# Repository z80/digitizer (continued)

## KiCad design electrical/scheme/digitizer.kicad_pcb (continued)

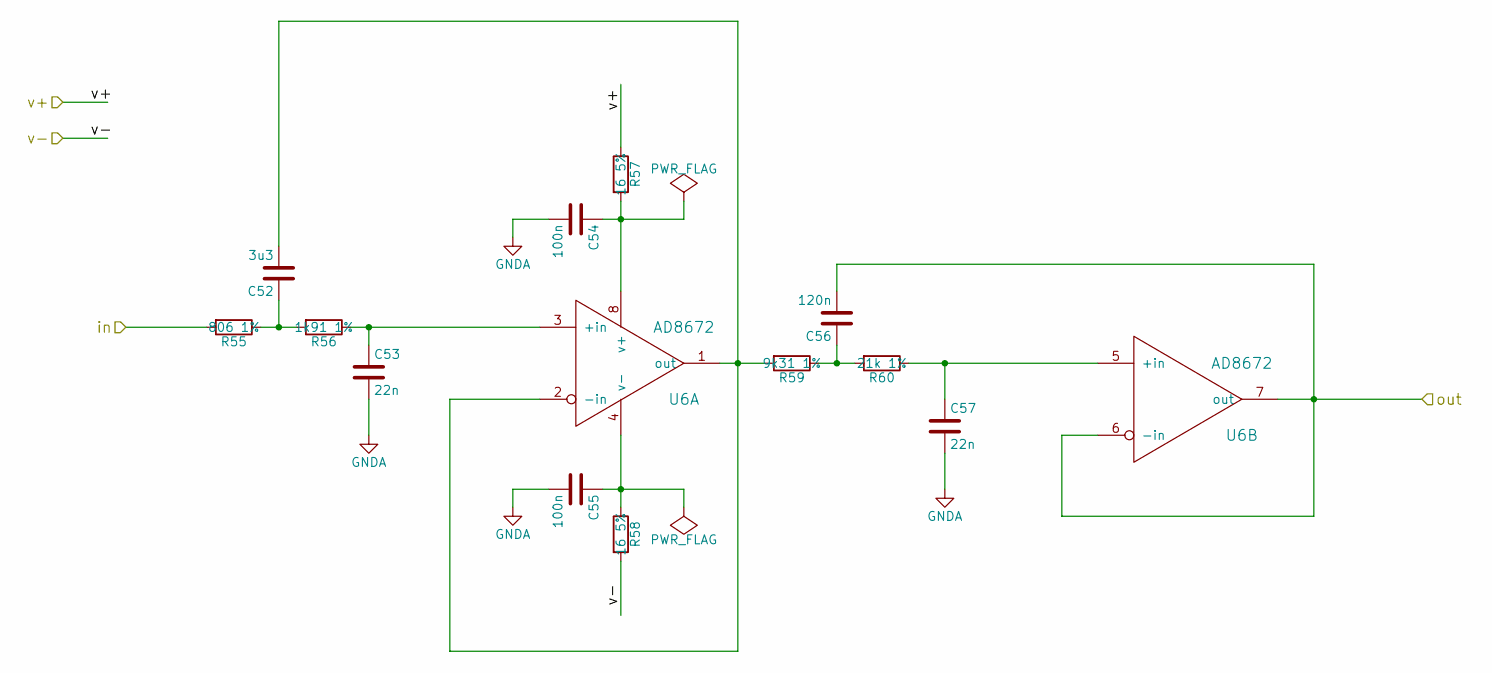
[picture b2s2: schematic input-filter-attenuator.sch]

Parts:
C40: 3u3; C_0805_HandSoldering
C41, C45: 22n; C_0805_HandSoldering
C42, C43: 100n; C_0805_HandSoldering
C44: 120n; C_0805_HandSoldering
R43: 806 1%; R_0805_HandSoldering
R44: 1k91 1%; R_0805_HandSoldering
R45, R46: 16 5%; R_0805_HandSoldering
R47: 9k31 1%; R_0805_HandSoldering
R48: 21k 1%; R_0805_HandSoldering
U4: AD8672; SOIC-8_3.9x4.9mm_Pitch1.27mm

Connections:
/dac-v-0/v+: R45.1; also elsewhere on the board
/dac-v-0/v-: R46.2; also elsewhere on the board
/input-filter-attenuator-0/in: R43.2; also elsewhere on the board
/input-filter-attenuator-0/out: C44.2, U4.6 (-in), U4.7 (out); also elsewhere on the board
GNDA: C41.2, C42.2, C43.2, C45.2; also elsewhere on the board
unnamed: C40.1, R43.1, R44.2
unnamed: C40.2, R47.2, U4.1 (out), U4.2 (-in)
unnamed: C41.1, R44.1, U4.3 (+in)
unnamed: C42.1, R45.2, U4.8 (v+)
unnamed: C43.1, R46.1, U4.4 (v-)
unnamed: C44.1, R47.1, R48.2
unnamed: C45.1, R48.1, U4.5 (+in)

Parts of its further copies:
C46, C52, C58: 3u3; C_0805_HandSoldering
C47, C51, C53, C57, C59, C63: 22n; C_0805_HandSoldering
C48, C49, C54, C55, C60, C61: 100n; C_0805_HandSoldering
C50, C56, C62: 120n; C_0805_HandSoldering
R49, R55, R61: 806 1%; R_0805_HandSoldering
R50, R56, R62: 1k91 1%; R_0805_HandSoldering
R51, R52, R57, R58, R63, R64: 16 5%; R_0805_HandSoldering
R53, R59, R65: 9k31 1%; R_0805_HandSoldering
R54, R60, R66: 21k 1%; R_0805_HandSoldering
U5, U6, U7: AD8672; SOIC-8_3.9x4.9mm_Pitch1.27mm

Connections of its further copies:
/dac-v-0/v+: R51.1, R57.1, R63.1; also elsewhere on the board
/dac-v-0/v-: R52.2, R58.2, R64.2; also elsewhere on the board
/input-filter-attenuator-1/in: R49.2; also elsewhere on the board
/input-filter-attenuator-1/out: C50.2, U5.6 (-in), U5.7 (out); also elsewhere on the board
/input-filter-attenuator-2/in: R55.2; also elsewhere on the board
/input-filter-attenuator-2/out: C56.2, U6.6 (-in), U6.7 (out); also elsewhere on the board
/input-filter-attenuator-3/in: R61.2; also elsewhere on the board
/input-filter-attenuator-3/out: C62.2, U7.6 (-in), U7.7 (out); also elsewhere on the board
GNDA: C47.2, C48.2, C49.2, C51.2, C53.2, C54.2, C55.2, C57.2, C59.2, C60.2, C61.2, C63.2; also elsewhere on the board
unnamed: C46.1, R49.1, R50.2
unnamed: C46.2, R53.2, U5.1 (out), U5.2 (-in)
unnamed: C47.1, R50.1, U5.3 (+in)
unnamed: C48.1, R51.2, U5.8 (v+)
unnamed: C49.1, R52.1, U5.4 (v-)
unnamed: C50.1, R53.1, R54.2
unnamed: C51.1, R54.1, U5.5 (+in)
unnamed: C52.1, R55.1, R56.2
unnamed: C52.2, R59.2, U6.1 (out), U6.2 (-in)
unnamed: C53.1, R56.1, U6.3 (+in)
unnamed: C54.1, R57.2, U6.8 (v+)
unnamed: C55.1, R58.1, U6.4 (v-)
unnamed: C56.1, R59.1, R60.2
unnamed: C57.1, R60.1, U6.5 (+in)
unnamed: C58.1, R61.1, R62.2
unnamed: C58.2, R65.2, U7.1 (out), U7.2 (-in)
unnamed: C59.1, R62.1, U7.3 (+in)
unnamed: C60.1, R63.2, U7.8 (v+)
unnamed: C61.1, R64.1, U7.4 (v-)
unnamed: C62.1, R65.1, R66.2
unnamed: C63.1, R66.1, U7.5 (+in)

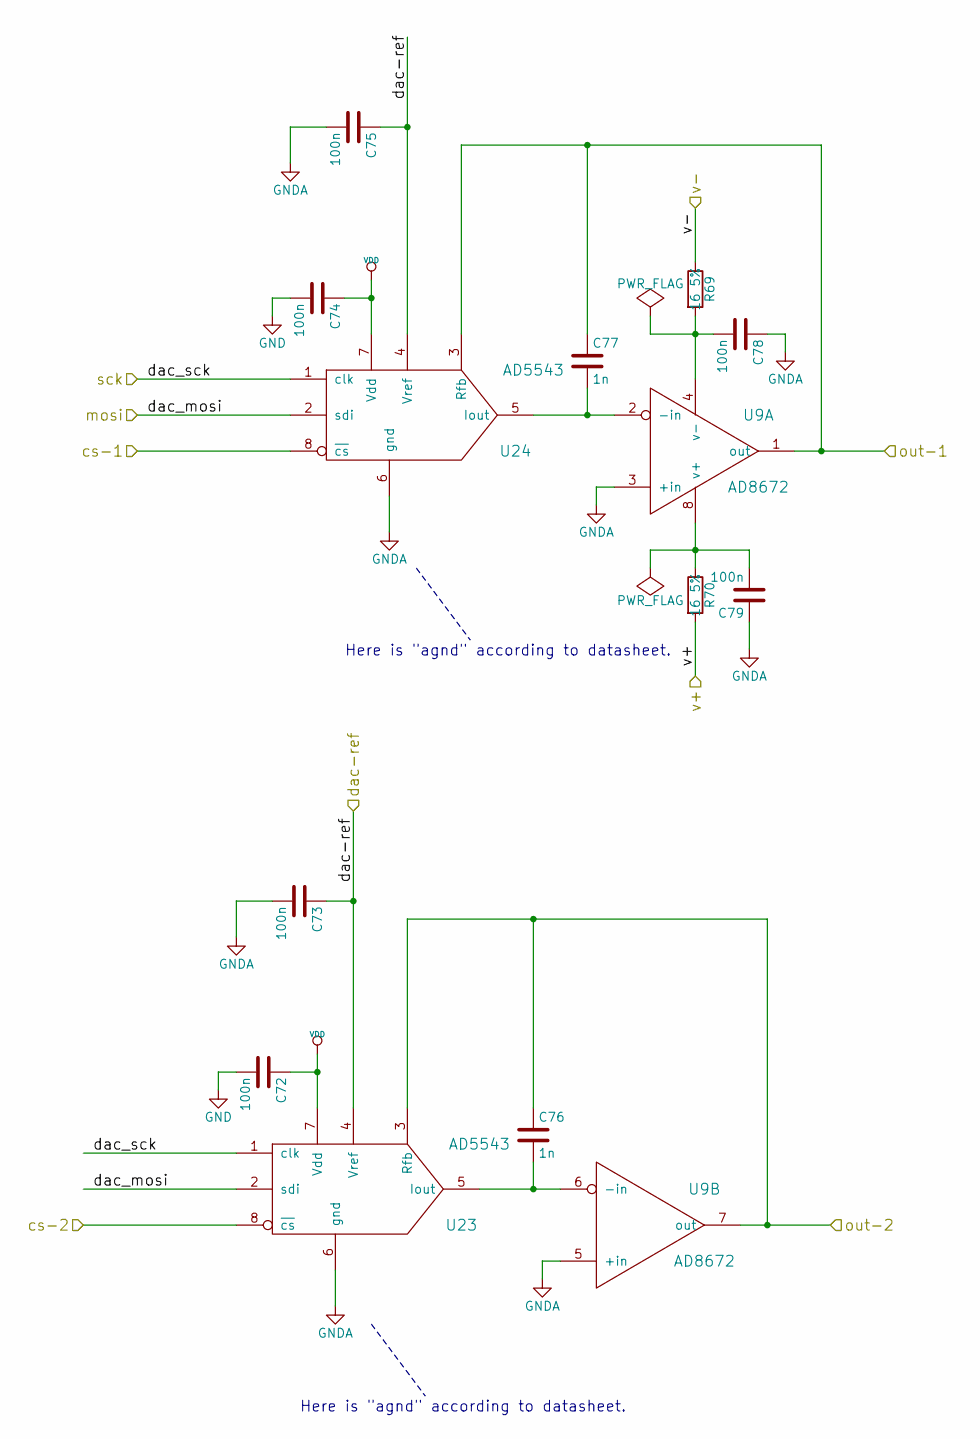
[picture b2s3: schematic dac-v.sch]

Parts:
C64, C65, C66, C67, C70, C71: 100n; C_0805_HandSoldering
C68, C69: 1n; C_0805_HandSoldering
R67, R68: 16 5%; R_0805_HandSoldering
U8: AD8672; SOIC-8_3.9x4.9mm_Pitch1.27mm
U21, U22: AD5543; SOIC-8_3.9x4.9mm_Pitch1.27mm

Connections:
/dac-v-0/cs-1: U22.8 (~cs~); also elsewhere on the board
/dac-v-0/cs-2: U21.8 (~cs~); also elsewhere on the board
/dac-v-0/dac-ref: C65.1, C67.1, U21.4 (Vref), U22.4 (Vref); also elsewhere on the board
/dac-v-0/mosi: U21.2 (sdi), U22.2 (sdi); also elsewhere on the board
/dac-v-0/out-1: C69.1, U8.1 (out), U22.3 (Rfb); also elsewhere on the board
/dac-v-0/out-2: C68.1, U8.7 (out), U21.3 (Rfb); also elsewhere on the board
/dac-v-0/sck: U21.1 (clk), U22.1 (clk); also elsewhere on the board
/dac-v-0/v+: R68.2; also elsewhere on the board
/dac-v-0/v-: R67.1; also elsewhere on the board
GND: C64.2, C66.2; also elsewhere on the board
GNDA: C65.2, C67.2, C70.1, C71.1, U8.3 (+in), U8.5 (+in), U21.6 (gnd), U22.6 (gnd); also elsewhere on the board
unnamed: C68.2, U8.6 (-in), U21.5 (Iout)
unnamed: C69.2, U8.2 (-in), U22.5 (Iout)
unnamed: C70.2, R67.2, U8.4 (v-)
unnamed: C71.2, R68.1, U8.8 (v+)
VDD: C64.1, C66.1, U21.7 (Vdd), U22.7 (Vdd); also elsewhere on the board

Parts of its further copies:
C72, C73, C74, C75, C78, C79: 100n; C_0805_HandSoldering
C76, C77: 1n; C_0805_HandSoldering
R69, R70: 16 5%; R_0805_HandSoldering
U9: AD8672; SOIC-8_3.9x4.9mm_Pitch1.27mm
U23, U24: AD5543; SOIC-8_3.9x4.9mm_Pitch1.27mm

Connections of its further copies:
/dac-v-0/dac-ref: C73.1, C75.1, U23.4 (Vref), U24.4 (Vref); also elsewhere on the board
/dac-v-0/v+: R70.2; also elsewhere on the board
/dac-v-0/v-: R69.1; also elsewhere on the board
/dac-v-1/cs-1: U24.8 (~cs~); also elsewhere on the board
/dac-v-1/cs-2: U23.8 (~cs~); also elsewhere on the board
/dac-v-1/mosi: U23.2 (sdi), U24.2 (sdi); also elsewhere on the board
/dac-v-1/out-1: C77.1, U9.1 (out), U24.3 (Rfb); also elsewhere on the board
/dac-v-1/out-2: C76.1, U9.7 (out), U23.3 (Rfb); also elsewhere on the board
/dac-v-1/sck: U23.1 (clk), U24.1 (clk); also elsewhere on the board
GND: C72.2, C74.2; also elsewhere on the board
GNDA: C73.2, C75.2, C78.1, C79.1, U9.3 (+in), U9.5 (+in), U23.6 (gnd), U24.6 (gnd); also elsewhere on the board
unnamed: C76.2, U9.6 (-in), U23.5 (Iout)
unnamed: C77.2, U9.2 (-in), U24.5 (Iout)
unnamed: C78.2, R69.2, U9.4 (v-)
unnamed: C79.2, R70.1, U9.8 (v+)
VDD: C72.1, C74.1, U23.7 (Vdd), U24.7 (Vdd); also elsewhere on the board

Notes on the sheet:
Here is "agnd" according to datasheet.

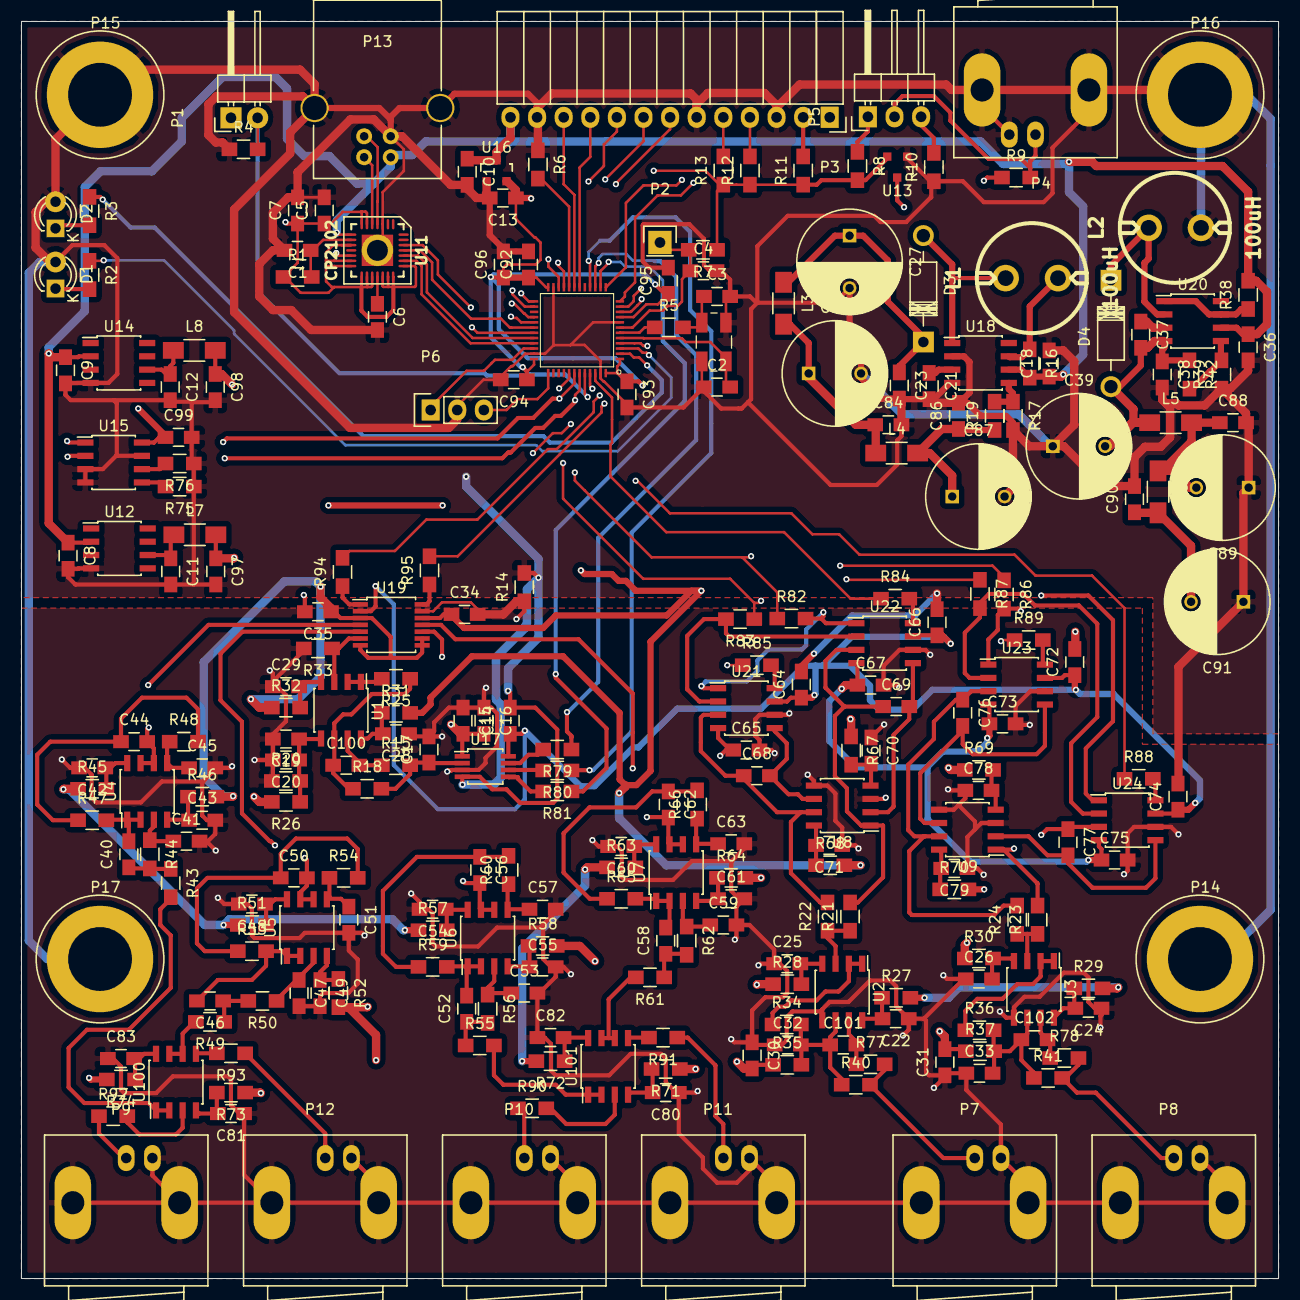
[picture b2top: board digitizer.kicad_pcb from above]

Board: 4 copper layers, 120.0 x 120.0 mm, 253 parts (0 on the bottom side), 163 nets.

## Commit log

2015-07-03 Annotated opamps.
2015-07-10 Added capacitors for making opamp driving capacitive load stable.
2015-07-10 Inserted holding screw holes.
2015-07-17 Placed all components. Now routing.
2015-07-20 Routing...
2015-07-20 Routing completed in the very first approximation.
2015-07-20 Normal BOM could be exported in "File->fabrication" falling menu.
2015-07-20 Inserting BOM into purchassing software.
2015-07-21 Generated gerbers.
2015-07-21 Prepared for OSHPark.
2015-07-22 Added firmware.
2015-07-24 Added software folder.
2015-07-24 Working on oscilloscope implementation in digitizer firmware.
2015-07-28 Making main high level control class.
2015-08-10 Debugging. SPI callback doesn't want working.
2015-08-11 Experimenting with different versions.
2015-08-12 It looks like ADC read works. But DAC still doesn't.
2015-08-12 Can't make 2-d and 3-rd DAC's CS pads work. (0-th and 1-st work properly due to some reason.)
2015-08-12 DAC works. Problem was caused by the fact that command queue was filled faster then it was purged by timer.
2015-08-12 Moved DAC control to dac_ctrl.c.
2015-08-13 Vesrions and instantAdc() work.
2015-08-13 setDac1() and setDac2() also work. And output votale range looks normal.
2015-08-13 GUI software somehaow lives. At last it shows something.
2015-08-13 Fixed random dac range.
2015-08-13 Made optimezed image. Recorded some data for DACs calibration.
2015-08-13 No corelation in DAC data.
2015-08-13 So actually DAcs work. Just tried plotting least significant one versus voltage. Of course it looked like noise.
2015-08-13 ADC works properly.
2015-08-14 Make idle clock high.
2015-08-14 aaaaaa
2015-08-15 Turned out that microcontroller performance is hardly enough to read 20kHz. And changed input filters into 2-d order + buffer to prevent multiplexor switches problem.
2015-08-15 Added some improvements. But if just 1kOhm resistor added in between filter and multiplexer it solves switch spike back propagation into filter. And it eliminates mutual signal interference.
2015-08-16 Added temperature sensor. Due to some reason data is quite discrete.
2015-08-17 Simplified ADC ISR.
2015-08-17 Made external interrupt driven sweep.
2015-08-17 Compiler wanted _exit(), _kill() and something else to be implemented. I've changed it to CodeSourcery. Now it doesn't want it :)
2015-08-17 Insering sweep functionality.
2015-08-18 Working on sweep.a
2015-08-18 Temperature readout still works. And due to error fixed it works much better.
2015-08-18 Made reading osc and sweep data in one and the sampe thread. Going to analyze interrupts lattency via GPIOs.
2015-08-18 Inserted debug output to GPIOs.
2015-08-18 Made interrupt priorities euqal. It still runs.
2015-08-19 Due to some reason DAC0 in the table of dac values applied is strange number.
2015-08-19 Sweep works at 10kHz.
2015-08-19 Sweep and oscilloscope work with median filtering.
2015-08-19 16kHz timer also works fine.
2015-08-19 Sweep window tile and data readout work.
2015-08-19 Inserted external trigger support.
2015-08-19 Fixed sweep interruption.
2015-08-20 Additional board for sending one of current signals to AFM.
2015-08-20 Fixed problems.
2015-08-21 Added AFM output control and filled firmware upgrade routine.
2015-08-21 Commented out GPIOs triggering from ISRs.
2015-08-21 Implemented bootloader.
2015-08-21 Fixed bootloader and verified firmware upgrade routine.
2015-08-21 Firmware upgrade more or less executes.
2015-08-21 In order to work with bootloader and with firmware inserted 500ms pauses in between bootloader commands.
2015-08-21 Fixed signals order.
2015-08-22 Soldered one board and attached to main board. It seems like it works.
2015-08-25 Designing case...
2015-08-28 Added washer for holding initially not planned BNC for output to AFM.
2015-08-28 Data with temperature.
2015-08-29 Added DAC data at different temperature.
2015-08-29 To be able to merge.
2015-08-29 Made finding best match.
2015-08-29 Returned back Eclipse project files.
2015-08-30 Removed wrong data from consideration.
2015-08-31 Trying to implement DAC calibrations.
2015-08-31 Removed unused data.
2015-09-01 Fixed gains.
2015-09-01 Save calibration file.
2015-09-01 Adjusted arguments order.
2015-09-01 Adjusted calibration file.
2015-09-01 Flipped sweep axes.
2015-09-01 Fixed external triggering.
2015-09-02 New calibration data gave better precission then previous one.
2015-09-02 Changed gain options.
2015-09-04 Made it running with ICE-3.5.1.
2015-09-04 Implemented Lua module.
2015-09-04 Added visibility toggling and units to plots.
2015-09-07 Added DAC mode to Sweep. And changed firmware version to 1.1.0.
2015-09-07 Changed icon and made loading and saving GUI data.
2015-09-08 Added icons.
2015-09-18 Started more appropriate sweeping implementation.
2015-09-18 Start debugging new sweep mode.
2015-09-18 Sweep works but at the very end behaves strange.
2015-09-18 Firmware version 1.2.0.
2015-09-18 Just made current values readable.
2015-09-21 Added installer code.
2015-09-21 Removed unused projects.
2015-09-24 Adjusted signal signs and GUI titles.
2015-09-29 Changed the way sweep data is triggered.
2015-09-29 Increased buffer size.
2015-09-29 Trying to minimize IO size.
2015-09-30 Rolled back all data sizes and it seems it works as before.
2015-09-30 Instant data 2 bytes works.
2015-09-30 Changed oscilloscope data to 2 bytes wide. Still alive.
2015-09-30 Limited writing buffer size to not overcome TX buffer capacity.
2015-09-30 Returned units conversion. It decreased maximum speed by 0.1Hz. It was 4.9Hz became 4.8Hz.
2015-10-01 To run on a blank computer.
2016-02-02 Inserted current sweep queue size query function.
2016-02-02 Designing cycled sweep.
2016-02-02 Implemented polarization via sweep with 0 transition time.
2016-02-03 Made a couple of corrections of initial state to make transitions smooth.
2016-02-03 Added software version information. Fixed sweep last point(s) obtaining.
2016-02-03 Inserted help window.
2016-02-03 Just one window is needed.
2016-02-05 Added points and rate limitations.
2016-02-05 Removed test code. For now with VCP driver reached maximum throughput of 500 points (one points is 4 2-byte words). Going to branch and tru USBXpress driver with higher transfer rates.
2016-02-06 USBXpress driver support is inplemented. But can't install device driver itself.
2016-02-24 Increased bootloader wait time to 5 seconds. As it seems it is impossible to engage firmwareUpgrade within 3 seconds. serial open procedure takes too long.
2016-02-24 Returned to uncontrolled io.
2016-02-24 In bootloader with increased time changed it's version to 1.0.1.
2016-02-24 Just in case if LEDs may provide any EMI turn them off when open a device.
2016-03-21 Slightly fixed Help document.
2016-06-10 Added flipping potentials, added current gain 1E3, changed software version to 1.0.1.
2016-06-11 Made recording for chonoamperometry.
2016-06-13 Changed software version to 1.1.0 and installer version to 1.3.0.
2016-07-08 Added I(t) recording and flippong output potentials.
2016-07-08 Implemented "pull" option for chonoamperometry.
2016-07-08 Changed sogtware version to 1.2.0.
